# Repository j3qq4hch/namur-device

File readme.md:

В это репозитории хранятся исходные файлы проекта промышленного контроллера с Namur-входами

## Соображения

Ниже приведена схема одного измерительного канала

Эта схема, хотя и не копирует 1 в 1, но все же весьма похожа на схему из контроллера Siemens SIMATIC ET200SP, ниже приведена картинки из [мануала](https://cache.industry.siemens.com/dl/files/246/109747246/att_921248/v1/et200sp_ha_di_16xnamur_manual_en-US_en-US.pdf) на этого контроллер (раздел 3.2).

Запитывать все каналы предполагается от шины питания 8.2 вольта, которая должна быть организована внутри устройства. Например, на DC-DC конвертере TPS54360:

При этом для создания шины 8.2 вольта может быть использована как внутренняя шина 24 В устройства, так и 24 вольта, подаваемые извне. 

## Количество каналов

Есть веские причины остановиться на 16 каналах для этого устройства. В пользу такого решения говорят следующие причины:

1) В этом устройстве конструктивно можно размеситить максимум 34-пиновый разъем для подключения датчиков. При этом типичный датчик имеет 2-проводную схему подключения. Хотя технически возможно увеличить количество каналов в 2 раза, монтаж в таком случае окажется крайне неряшливый и неудобный. 
2) В микроконтроллере stm32f412 16-канальный АЦП. В случае бОльшего количества каналов пришлось бы использовать дополнительные аналоговые коммутаторы. А с 16 каналами можно обойтись только микроконтроллером. Меньше BoM, проще устройство. 
3) Если на практике требуется больше 16 каналов Namur (что вообще-то не так уж и мало), можно просто установить дополнительные устройства.

## Версия на 32 канала

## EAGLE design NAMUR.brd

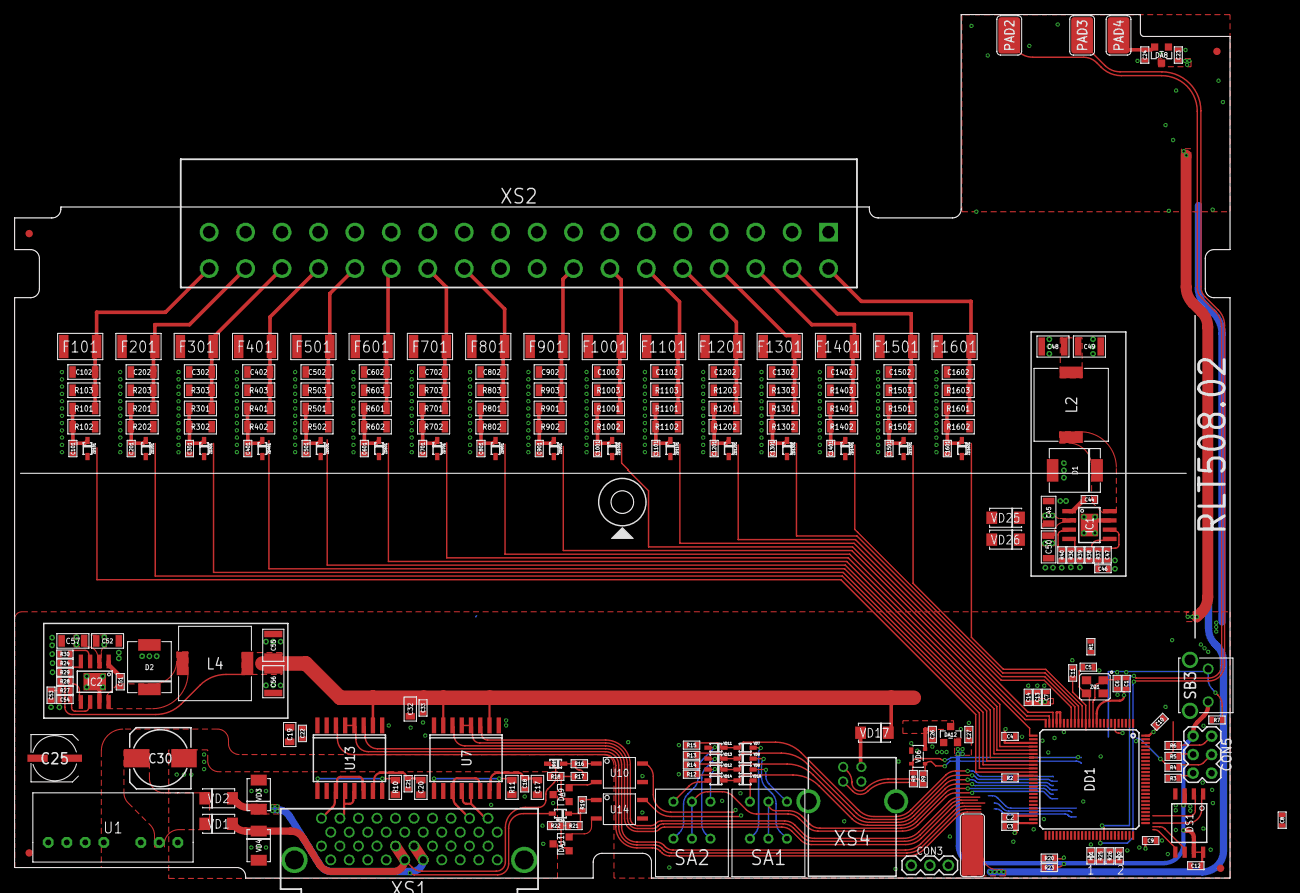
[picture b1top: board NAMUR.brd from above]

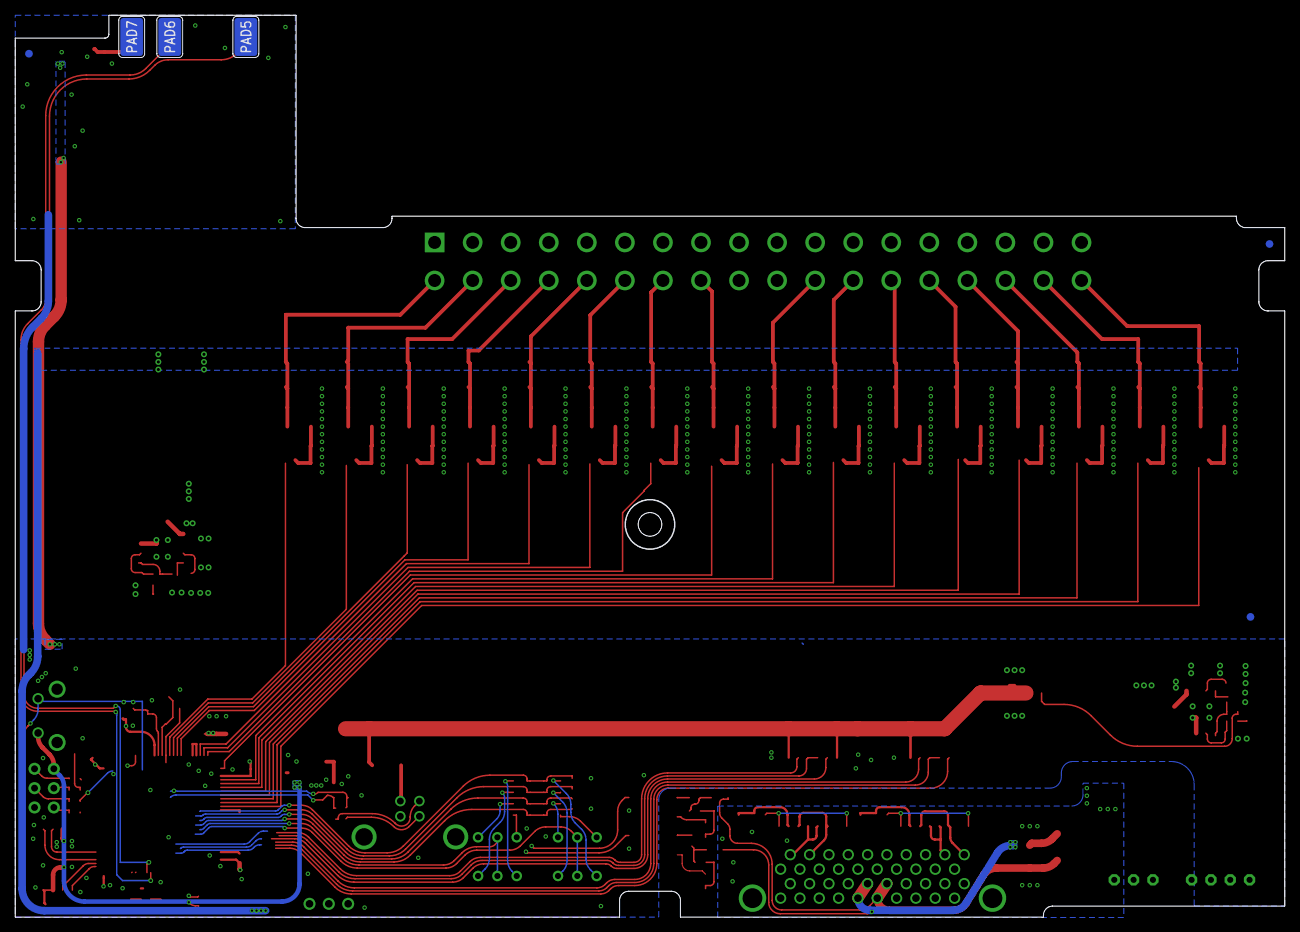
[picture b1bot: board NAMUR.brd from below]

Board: 4 copper layers, 166.8 x 118.5 mm, 250 parts (6 on the bottom side), 121 nets.

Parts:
C1, C3, C4, C7, C9, C10, C11, C12, C13, C18, C21, C22, C23, C24, C26, C27, C33, C44, C51: 0.1u; C0603
C2, C8: 2.2u; C0603
C5, C6: 12p; C0603
C14: 1u; C0603
C17, C19, C20, C32: 10u; C0805
C25: 22u; CAP_SMD_6.3X7.7
C30: 100u; SMD-0810
C45, C50, C52, C57: 2.2u; C1206
C46, C53: 6800p; C0603
C47, C54: 39p; C0603
C48, C49, C55, C56: 10u; C1210
C101, C201, C301, C401, C501, C601, C701, C801, C901, C1001, C1101, C1201, C1301, C1401, C1501, C1601: 10n; C0603
C102, C202, C302, C402, C502, C602, C702, C802, C902, C1002, C1102, C1202, C1302, C1402, C1502, C1602: 4700p; C1206
CON3: PINHEAD_1X03-2.54; PLS3
CON5: PINHEAD_2X03-PTH-2.54; PLD6
D1, D2: B560C; DO-214AB(SMC)
DA8, DA12: XC6206P332; SOT23-3
DA9, DA11: TL431; SOT23-3
DD1: STM32F411VCT6; LQFP100
DS1: AT25DF321A; SOIC8-208MIL
F101, F201, F301, F401, F501, F601, F701, F801, F901, F1001, F1101, F1201, F1301, F1401, F1501, F1601: SURGE_ARRESTER-S30-A90X; S30-A90X
FD1, FD2, FD3, FD4, FD5, FD6, FD7: FIDUCIALMOUNT; FIDUCIAL_MOUNT
HL1, HL2: LED-0603; LED0603
IC1, IC2: TPS54360; SOIC8-POWERPAD
L2, L4: 8.2uH; CDRH105R
PAD1: PAD-8.3X3; 8.3X3
PAD2, PAD3, PAD4, PAD5, PAD6, PAD7: PAD-5X3; 5X3
R1, R2, R7, R12, R13, R14, R15, R20, R23, R29: 10K; R0603
R3, R4, R5, R6, R8, R9: 22R; R0603
R10, R11: 000; R0805
R16, R19: 4K7; R0603
R17, R21, R38: 75K; R0603
R18, R22: 24K; R0603
R24, R36: 143K; R0603
R25, R26: 1K; R0603
R27, R30, R37, R40: 18K; R0603
R28: 53K6; R0603
R39: 8K2; R0603
R101, R201, R301, R401, R501, R601, R701, R801, R901, R1001, R1101, R1201, R1301, R1401, R1501, R1601: 47K; R1206
R102, R202, R302, R402, R502, R602, R702, R802, R902, R1002, R1102, R1202, R1302, R1402, R1502, R1602: 33K; R1206
R103, R203, R303, R403, R503, R603, R703, R803, R903, R1003, R1103, R1203, R1303, R1403, R1503, R1603: 1K; R1206
SA1, SA2: DRD16RAE04
SB3: TACT_SWITCH-KLS-KLS7-TS6606; KLS7-TS6606-5.0-180
SCR1: SCREW-M3-D3.1; PCB_SCREW_M3-D3.1
U1: URB2424S-6WR3; URB_S-6WR3
U7, U13: NSIP83086(V); SOIC16-300MIL
U10, U14: KAQY214-SOP-4; SOP-4
VD1, VD2, VD17, VD25, VD26: SS34; DO-214AC(SMA)
VD3, VD4: SMBJ24CA-SMB; DO-214AA(SMB)
VD6: PRTR5V0U2X; SOT143B
VD7, VD8, VD9, VD10, VD11, VD12, VD13, VD14: BAT54JFILM; SOD323
VD15, VD16: BAV21WS; SOD323
XS1: 1734037-4
XS2: CCDN2,5/18-G1P26THR; CCDN2.5_18-G1P26THR
XS4: USB-TYPE-B; USB-B
ZD101, ZD201, ZD301, ZD401, ZD501, ZD601, ZD701, ZD801, ZD901, ZD1001, ZD1101, ZD1201, ZD1301, ZD1401, ZD1501, ZD1601: MM3Z3V3; SOD323
ZQ1: 8MHz; OSCILLATOR-3.2X2.5-4P

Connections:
1N: R15.2, VD7.C, VD11.C
2N: R14.2, VD8.C, VD12.C
4N: R13.2, VD9.C, VD13.C
8N: R12.2, VD10.C, VD14.C
!NRST: C11.2, DD1.14, R1.1, R3.1
ADC0: C101.2, DD1.23, R101.P$1, R102.P$2, ZD101.C
ADC1: C201.2, DD1.24, R201.P$1, R202.P$2, ZD201.C
ADC2: C301.2, DD1.25, R301.P$1, R302.P$2, ZD301.C
ADC3: C401.2, DD1.26, R401.P$1, R402.P$2, ZD401.C
ADC4: C501.2, DD1.29, R501.P$1, R502.P$2, ZD501.C
ADC5: C601.2, DD1.30, R601.P$1, R602.P$2, ZD601.C
ADC6: C701.2, DD1.31, R701.P$1, R702.P$2, ZD701.C
ADC7: C801.2, DD1.32, R801.P$1, R802.P$2, ZD801.C
ADC8: C901.2, DD1.35, R901.P$1, R902.P$2, ZD901.C
ADC9: C1001.2, DD1.36, R1001.P$1, R1002.P$2, ZD1001.C
ADC10: C1101.2, DD1.15, R1101.P$1, R1102.P$2, ZD1101.C
ADC11: C1201.2, DD1.16, R1201.P$1, R1202.P$2, ZD1201.C
ADC12: C1301.2, DD1.17, R1301.P$1, R1302.P$2, ZD1301.C
ADC13: C1401.2, DD1.18, R1401.P$1, R1402.P$2, ZD1401.C
ADC14: C1501.2, DD1.33, R1501.P$1, R1502.P$2, ZD1501.C
ADC15: C1601.2, DD1.34, R1601.P$1, R1602.P$2, ZD1601.C
BOOT0: DD1.94, R7.2, SB3.1
BOOT1: DD1.37, R2.2
BOOT4: C44.1, IC1.1
BOOT5: C51.1, IC2.1
CN1: SA1.C_1, SA1.C_2
CN2: SA2.C_1, SA2.C_2
DIN: C45.P$2, C50.P$2, IC1.2, VD25.C, VD26.C
EN: IC1.3, IC2.3, R30.2, R40.2
GND: C1.1, C2.1, C3.1, C4.1, C5.1, C6.2, C7.1, C8.1, C9.1, C10.2, C11.1, C12.1, C13.1, C14.1, C19.1, C22.1, C23.1, C24.1, C25.-, C26.1, C27.1, C32.1, C33.1, C45.P$1, C46.1, C47.1, C48.1, C49.1, C50.P$1, C52.P$1, C53.1, C54.1, C55.1, C56.1, C57.P$1, C101.1, C102.P$1, C201.1, C202.P$1, C301.1, C302.P$1, C401.1, C402.P$1, C501.1, C502.P$1, C601.1, C602.P$1, C701.1, C702.P$1, C801.1, C802.P$1, C901.1, C902.P$1, C1001.1, C1002.P$1, C1101.1, C1102.P$1, C1201.1, C1202.P$1, C1301.1, C1302.P$1, C1401.1, C1402.P$1, C1501.1, C1502.P$1, C1601.1, C1602.P$1, CON3.1, CON5.6, D1.A, D2.A, DA8.1, DA12.1, DD1.10, DD1.20, DD1.27, DD1.49, DD1.74, DD1.99, DS1.4, HL1.C, HL2.C, IC1.7, IC1.POWERPAD, IC2.7, IC2.POWERPAD, PAD5.P$1, PAD6.P$1, PAD7.P$1, R2.1, R7.1, R12.1, R13.1, R14.1, R15.1, R24.1, R29.1, R30.1, R36.1, R39.1, R40.1, R102.P$1, R103.P$1, R202.P$1, R203.P$1, R302.P$1, R303.P$1, R402.P$1, R403.P$1, R502.P$1, R503.P$1, R602.P$1, R603.P$1, R702.P$1, R703.P$1, R802.P$1, R803.P$1, R902.P$1, R903.P$1, R1002.P$1, R1003.P$1, R1102.P$1, R1103.P$1, R1202.P$1, R1203.P$1, R1302.P$1, R1303.P$1, R1402.P$1, R1403.P$1, R1502.P$1, R1503.P$1, R1602.P$1, R1603.P$1, U1.7, U7.1, U7.8, U10.3, U13.1, U13.8, U14.3, VD6.1, XS4.4, XS4.5_1, XS4.5_2, ZD101.A, ZD201.A, ZD301.A, ZD401.A, ZD501.A, ZD601.A, ZD701.A, ZD801.A, ZD901.A, ZD1001.A, ZD1101.A, ZD1201.A, ZD1301.A, ZD1401.A, ZD1501.A, ZD1601.A, ZQ1.2, ZQ1.4
GNDD: F101.2, F201.2, F301.2, F401.2, F501.2, F601.2, F701.2, F801.2, F901.2, F1001.2, F1101.2, F1201.2, F1301.2, F1401.2, F1501.2, F1601.2, PAD1.P$1
I2C3_SCL: DD1.67, PAD2.P$1
I2C3_SDA: DD1.66, PAD3.P$1
ISO24V: C30.+, U1.2, VD1.C, VD2.C
MCU_RX1: DD1.69, U13.3
MCU_RX6: DD1.64, U7.3
MCU_TX1: DD1.68, U13.6
MCU_TX6: DD1.63, U7.6
unnamed: C2.2, DD1.48
unnamed: C8.2, DD1.73
unnamed: CON5.5, R3.2
unnamed: C6.1, DD1.12, ZQ1.1
unnamed: C5.2, DD1.13, ZQ1.3
unnamed: CON5.4, R4.2
unnamed: CON5.3, R5.2
unnamed: CON5.2, R6.2
unnamed: DA9.2, U10.2
unnamed: DA9.1, R17.2, R18.1
unnamed: R16.1, U10.1
unnamed: R16.2, R17.1, VD15.C
unnamed: HL1.A, R25.2
unnamed: DA11.2, U14.2
unnamed: DA11.1, R21.2, R22.1
unnamed: R19.1, U14.1
unnamed: R19.2, R21.1, VD16.C
unnamed: HL2.A, R26.2
unnamed: IC1.4, R36.2
unnamed: C47.2, IC1.6, R37.2
unnamed: C46.2, R37.1
unnamed: IC1.5, R38.1, R39.2
unnamed: IC2.4, R24.2
unnamed: C54.2, IC2.6, R27.2
unnamed: C53.2, R27.1
unnamed: IC2.5, R28.1, R29.2
unnamed: R11.2, U7.9, U7.16
unnamed: C20.1, C21.1, U13.15
unnamed: C24.2, DA8.2, PAD4.P$1
unnamed: VD1.A, VD4.C, VD15.A, XS1.A5, XS1.B5
unnamed: VD2.A, VD3.C, VD16.A, XS1.A6, XS1.B6
unnamed: U7.11, U7.14, XS1.D9
unnamed: U7.12, U7.13, XS1.D10
unnamed: R10.2, U13.9, U13.16
unnamed: R9.2, XS4.2
unnamed: R8.2, XS4.3
unnamed: VD17.A, XS4.1
unnamed: U13.11, U13.14, XS1.D1
unnamed: U13.12, U13.13, XS1.D2
unnamed: C17.1, C18.1, U7.15
unnamed: SA1.1, VD7.A
unnamed: SA1.2, VD8.A
unnamed: SA1.4, VD9.A
unnamed: SA1.8, VD10.A
unnamed: SA2.1, VD11.A
unnamed: SA2.2, VD12.A
unnamed: SA2.4, VD13.A
unnamed: SA2.8, VD14.A
NAMUR0: C102.P$2, F101.1, R101.P$2, R103.P$2, XS2.B18
NAMUR1: C202.P$2, F201.1, R201.P$2, R203.P$2, XS2.B17
NAMUR2: C302.P$2, F301.1, R301.P$2, R303.P$2, XS2.B16
NAMUR3: C402.P$2, F401.1, R401.P$2, R403.P$2, XS2.B15
NAMUR4: C502.P$2, F501.1, R501.P$2, R503.P$2, XS2.B14
NAMUR5: C602.P$2, F601.1, R601.P$2, R603.P$2, XS2.B13
NAMUR6: C702.P$2, F701.1, R701.P$2, R703.P$2, XS2.B12
NAMUR7: C802.P$2, F801.1, R801.P$2, R803.P$2, XS2.B11
NAMUR8: C902.P$2, F901.1, R901.P$2, R903.P$2, XS2.B8
NAMUR9: C1002.P$2, F1001.1, R1001.P$2, R1003.P$2, XS2.B7
NAMUR10: C1102.P$2, F1101.1, R1101.P$2, R1103.P$2, XS2.B6
NAMUR11: C1202.P$2, F1201.1, R1201.P$2, R1203.P$2, XS2.B5
NAMUR12: C1302.P$2, F1301.1, R1301.P$2, R1303.P$2, XS2.B4
NAMUR13: C1402.P$2, F1401.1, R1401.P$2, R1403.P$2, XS2.B3
NAMUR14: C1502.P$2, F1501.1, R1501.P$2, R1503.P$2, XS2.B2
NAMUR15: C1602.P$2, F1601.1, R1601.P$2, R1603.P$2, XS2.B1
PGND: C17.2, C18.2, C20.2, C21.2, C30.-, DA9.3, DA11.3, R10.1, R11.1, R18.2, R22.2, U1.1, VD3.A, VD4.A, XS1.A1, XS1.A2, XS1.A3, XS1.A4, XS1.A7, XS1.A8, XS1.A9, XS1.B1, XS1.B2, XS1.B3, XS1.B4, XS1.B7, XS1.B8, XS1.B9, XS1.C4, XS1.C5, XS1.C6, XS1.C7, XS1.C8, XS1.D3, XS1.D6
REDE1: U13.4, U13.5
REDE2: DD1.65, U7.4, U7.5
SPI2_CLK: DD1.52, DS1.6
SPI2_CS: DD1.51, DS1.1
SPI2_MISO: DD1.53, DS1.2
SPI2_MOSI: DD1.54, DS1.5
SW10: C51.2, D2.C, IC2.8, L4.1
SW11: C44.2, D1.C, IC1.8, L2.1
SWC: DD1.76, R5.1
SWD: DD1.72, R6.1
U1TS: R20.1, U10.4
U2TS: R23.1, U14.4
USB_DM: DD1.70, R9.1, VD6.3
USB_DP: DD1.71, R8.1, VD6.2
VDD_3V3: C1.2, C3.2, C4.2, C7.2, C9.2, C10.1, C12.2, C13.2, C14.2, C27.2, CON5.1, DA12.2, DD1.6, DD1.11, DD1.21, DD1.22, DD1.28, DD1.50, DD1.75, DD1.100, DS1.3, DS1.7, DS1.8, R1.2, R20.2, R23.2, SB3.2
VDD_5V: C19.2, C22.2, C23.2, C26.2, C32.2, C33.2, C55.2, C56.2, DA8.3, DA12.3, L4.2, R28.2, U7.2, U7.7, U13.2, U13.7, VD6.4, VD17.C
VDD_8V2: C48.2, C49.2, L2.2, R38.2, XS2.A1, XS2.A2, XS2.A3, XS2.A4, XS2.A5, XS2.A6, XS2.A7, XS2.A8, XS2.A9, XS2.A10, XS2.A11, XS2.A12, XS2.A13, XS2.A14, XS2.A15, XS2.A16, XS2.A17, XS2.A18
VDD_24V: C25.+, C52.P$2, C57.P$2, IC2.2, U1.6, VD25.A

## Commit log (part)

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2026-06-30 some docs
